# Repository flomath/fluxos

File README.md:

# About
Fluxos is a tiny monolithic operating system for audio applications. Its an educational project at Vorarlberg University of Applied Sciences and features a simple scheduler, virtual memory management and a basic audio application on top.

## Documentation
Find a detailed documentation of this project on the github pages [http://flomath.github.io/fluxos/](http://flomath.github.io/fluxos/).

## Project status

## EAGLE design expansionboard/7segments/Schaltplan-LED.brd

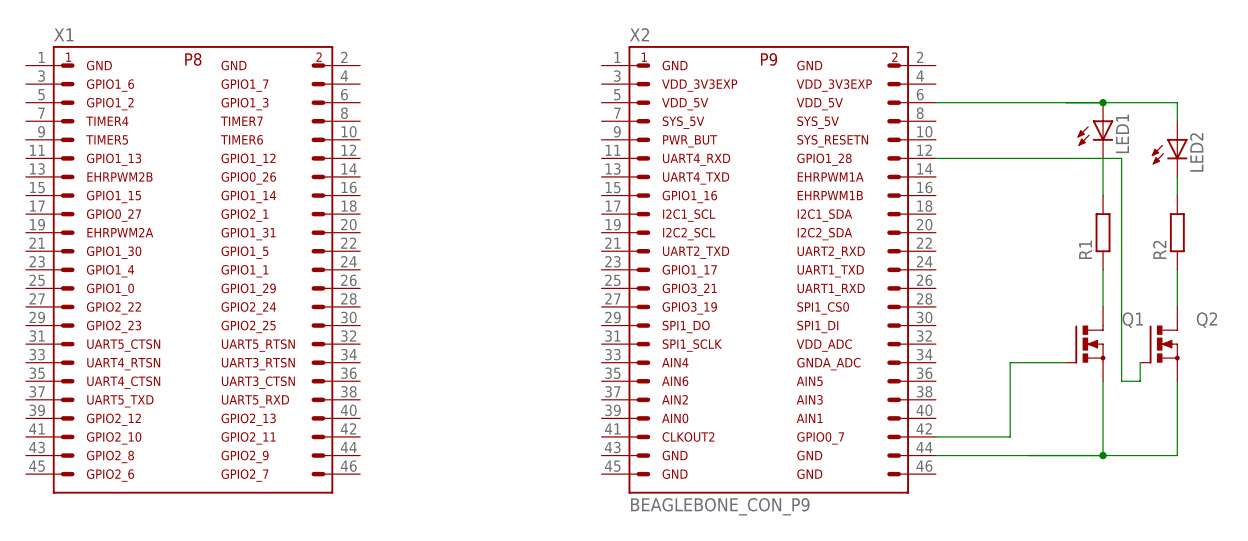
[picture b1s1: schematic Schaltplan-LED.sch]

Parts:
LED1, LED2: LEDCHIP-LED0603; CHIP-LED0603
Q1, Q2: N-MOSFET-SO8S; SO-08
R1, R2: R-EU_R0603; R0603
X1: BEAGLEBONE_CON_P8; 23X2_2-54
X2: BEAGLEBONE_CON_P9; 23X2_2-54

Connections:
unnamed: LED1.A, LED2.A, X2.6
unnamed: LED1.C, R1.2
unnamed: Q1.4 (G), X2.42
unnamed: Q1.5 (D), Q1.6 (D), Q1.7 (D), Q1.8 (D), R1.1
unnamed: Q1.1 (S), Q1.2 (S), Q1.3 (S), Q2.1 (S), Q2.2 (S), Q2.3 (S), X2.44
unnamed: LED2.C, R2.2
unnamed: Q2.4 (G), X2.12
unnamed: Q2.5 (D), Q2.6 (D), Q2.7 (D), Q2.8 (D), R2.1

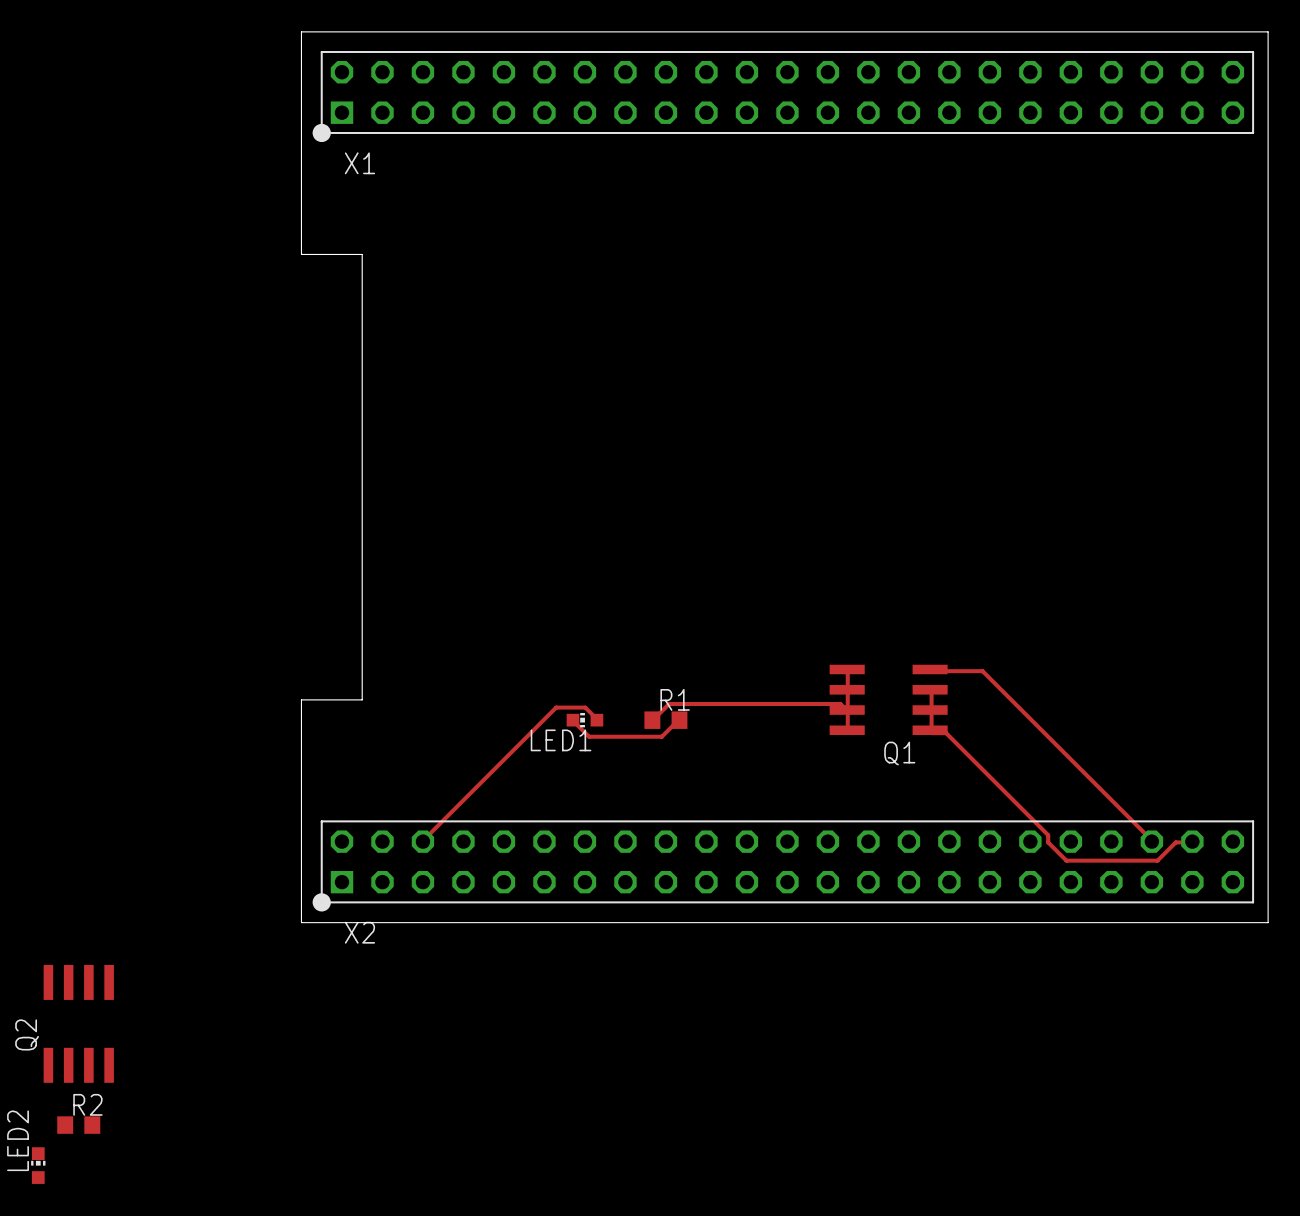
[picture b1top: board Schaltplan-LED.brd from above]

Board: 2 copper layers, 60.6 x 55.9 mm, 9 parts (0 on the bottom side), 8 nets.

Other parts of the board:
U$1: BEAGLEBONE-OUTLINE

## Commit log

2015-02-25 add waffle.io badge
2015-02-25 added github issue badge to readme
2015-02-27 Create gh-pages branch via GitHub
2015-02-27 Trying to add a demo page
2015-02-27 renamed demo
2015-02-27 Added title
2015-02-27 Removed demo.markdown
2015-02-27 removed auto generated files
2015-02-27 Update Readme
    Add link to pages
2015-02-27 Baseurl for fhv-os
2015-02-27 Added gemfile
2015-02-27 removed _site directory
2015-02-27 added new file
2015-02-27 removed pages dir
2015-02-27 added gitignore for _pages and -sites
2015-02-27 wrote the first pages on project management
2015-02-27 updated config and index file
2015-02-27 fixed a bug i previously added to the config file
2015-03-12 setup code composer project
2015-03-12 basic uart based on omap35x programming model
2015-03-13 Added systems page for kernel and omap documentation
2015-03-13 changed the name to fluxos, unified all header styles
2015-03-13 changed name to fluxos (including repository)
2015-03-13 changed name to fluxos
2015-03-13 implemented uart programming model based on omap
2015-03-13 added dma description out of the omap guide
2015-03-18 fixed some compile errors
2015-03-18 Added doxygen file
    Added doxygen for documentation and ignored output file
2015-03-18 added boot.asm and started testing the UART settings
2015-03-18 Added UartDriver
    also commented the hal/uart
2015-03-18 added travis build configuration
2015-03-18 added travis doxygen cmd by github.com/miloyip/rapidjson
2015-03-18 updated travis path
2015-03-18 travis config to skip gcc build
2015-03-18 Added travis status
    Well.. we are not actually building with it, but anyways :wink:
2015-03-18 removed weird badge
2015-03-18 again some updates to the travis configuration
2015-03-18 unfortunately pushed wrong script file
2015-03-18 Fixed Compiler errors
2015-03-18 Update travis
2015-03-18 Cleaned hal
2015-03-18 Updated doxygen build script
2015-03-18 Removed security check
2015-03-18 Automatic doxygen build
2015-03-18 Fixed the beagleboard.cmd in order to hook up our init method, UART init should work by now
2015-03-18 Changed doxygen command
2015-03-18 Revert "Automatic doxygen build"
    This reverts commit d3dead3f54b3b97974bb6c58bd8f0381ef055f79.
2015-03-18 Revert "Automatic doxygen build"
    This reverts commit 58535501b95a1a945c862df11eb9ca8b59eb89c9.
2015-03-19 added RS232 section in documentation
2015-03-19 Update doxygen command for travis
2015-03-19 Fixed forgotten path
2015-03-19 Updating doxygen command again
2015-03-19 restructured hal, added missing uart methods
2015-03-19 Update doxygen command for travis again...
2015-03-19 Fixed paths
2015-03-19 Use newer doxygen version
2015-03-19 Fixed input path
2015-03-19 Add .nojekyll file to Doxygen Folder
2015-03-19 Add .nojekyll file to Doxygen Folder (different function)
2015-03-19 Updating doxygen the last time
2015-03-19 HAL-layer prototype
2015-03-19 Adding nojekyll file to top directory
2015-03-19 Including doxygen
2015-03-19 Including doxygen #2
2015-03-19 Adding .nojekyll again for tests
2015-03-19 deleted nojekyll again
2015-03-19 Adding .nojekyll for testing purposes
2015-03-19 Deleting it...
2015-03-19 Update _config.yml
    test for keeping the files in doxygen directory
2015-03-19 Update _config.yml
    further test for keeping files
2015-03-19 Update _config.yml
    fixed typo
2015-03-19 refactored the directory layout, added common dir for generic implementations
2015-03-19 Update _config.yml
    local running jekyll
2015-03-19 added first version of gp timers
2015-03-20 UART sending
    - Fixed #3
2015-03-25 fixed compiler error
2015-03-25 Update README.md
    fixed url to new repository
2015-03-25 first version of scheduler and process structure
2015-03-25 updated main for ccs project
2015-03-25 reversed everything i did today - didn't think much about it i guess
2015-03-26 groundwork for upcoming context switches with mmu #7
2015-03-26 added timer init and start methods #13
2015-03-26 timer init #13
2015-03-26 Use 32Bitmask for Registers
2015-03-26 First interrupts occuring
    Howver, they are not the ones we want ...
2015-03-26 fixed end of line error
2015-03-26 Implementing enable interrupt method
    Anyway it is not used yet
2015-03-26 info about timer
2015-03-26 moved interface methods to common, added disable interrupt method
2015-03-27 changed about section in readme
2015-03-27 fixed a register define #13
2015-03-27 Fixed Interrupt Stack
2015-03-27 Starting the timer
2015-03-27 Testing timers
2015-03-28 Interrupt Callbacks are now called by the IRQ Handler
2015-03-28 Adding header file for Power Management
    However not used, because everything is ENABLED by default
2015-04-02 new timer setting as in reference guide p.2615
2015-04-02 Ensure correct register size
2015-04-02 added timer implementation details
2015-04-02 updated scrum sprints
2015-04-02 Receiving (only) first character
    - by a timeout
    - exception because reentering the ISR
2015-04-08 Removed #pragma TASK because it won't save the LR from the IRQ so that it won't go back
2015-04-08 added timers 3 to 9, but only working as 1ms ticks
2015-04-09 Updated documentation: Interrupts
    Added interrupts to the documentation
2015-04-09 Fixed path for GH Pages
2015-04-09 did nothing
2015-04-09 scheduler running with timer interval, except if you add an endless loop in your tasks (do we need to leave the interrupt mode first?)
2015-04-09 First prototype of mmu, mmu can be enabled now - settings have to be defined correctly
2015-04-09 Added UART as Process
2015-05-13 added expansion board brd files for eagle
2015-05-13 WIP Temporarly save Context
2015-05-13 added clock and gpio using programming model, not yet tested
2015-05-14 prototype of mmu and memory manager (need to be tested + dabt handler not implemented yet)
2015-05-14 gpio and button is triggering a interrupt, leds do not work currently
2015-05-14 WIP Context Switch
2015-05-14 "mmu enable" is working now, introduced NULL and bool type
2015-05-14 removed unnecessary functions
2015-05-14 added source files for mcbsp
2015-05-20 l2 and page frames
2015-05-20 WIP Context Load seems to work
2015-05-20 L1, L2 and page frames (waiting for correct interrupt), added process functions to mmu
2015-05-22 Scheduling between the first 3 Processes works, however the value in the USER-LR of PID#0 is 0, therefore a DataAbort Exception occurs
2015-05-23 moved regions, added some todos
2015-05-23 added system calls (working,except after switching back to context)
2015-05-23 Context is now saved to Stack and load from there,
    however I still get some PABT Exceptions after one round
2015-05-23 Disabled printfs ... Seems to be working now
2015-05-24 CS working :)
2015-05-28 adjusted for new process struc
2015-05-29 init commit for filesystem
2015-05-30 save of current state, dabts working -> l2 gets overwritten!
2015-05-30 mmu is working now (seems to) - killing processes still not implemented
2015-05-30 clear the interrupt flag afterwards, otherwise interrupt is called twice
2015-06-03 mmu can kill a process now
2015-06-04 no function call for setting a bit
2015-06-04 Audio development started: Enabled MCBSP2
2015-06-04 removed unused function, printfs..
2015-06-04 extended hal to 32bit, added mmcsd settings
2015-06-04 mmcsd programming guide no. 2
2015-06-07 send commands, and following the programming guide - part 3
2015-06-10 i2c header added
    We will need TPS65950 for audio which is controlled by I2C
2015-06-10 moved irq clearing, process exit handler(need to be extracted as syscall)
2015-06-10 Revert "Merge branch 'filesystem' of https://github.com/flomath/fluxos"
    This reverts commit 4ed08148a070b577ef70f09ed236475965b2041b, reversing
    changes made to 992f4ce8624f184f5e2a38e5c143661ae7149a18.
2015-06-10 fixed reading value calls
2015-06-10 Inline must be in header
2015-06-10 Project settings
2015-07-01 Started a first process... I guess
2015-07-01 missing file
2015-07-01 setting up mmcsd, next step: send cmd
2015-07-02 Tested UART
2015-07-02 working on audio initialization
2015-07-02 process killing is working now
2015-07-02 Still working on audio configuration
2015-07-02 still working on detecting sd card, failing at busy flag
2015-07-02 wrong clock selected, still no luck
2015-07-03 console/uart test
2015-07-03 forgot to commit new files
2015-07-03 work in progress
2015-07-03 working on mmcsd settings
2015-07-03 New Application added
2015-07-03 changed sysapi
2015-07-03 Changed Project settings to enable hex output
2015-07-03 Application One added and Build problem fixed
2015-07-03 Changed Stack Position
2015-07-03 Print from Application
2015-07-03 Added syscall for loading processes, changed loader function
2015-07-03 working version beta 0.1
2015-07-03 removed unused pcb params
2015-07-03 again, some changes - no luck
2015-07-03 working copy of detecting card
2015-07-03 read and write methods for sd card
2015-07-03 Created a semaphore
2015-07-03 Creating and Destroying Semaphores
2015-07-04 uart_read in console has to checked
2015-07-04 Using semaphore for UART; Problem: irqs do not occur during syscall
2015-07-04 some changes, no luck again
2015-07-04 semaphore seems to be working when printfs are there. Without them it won't work
2015-07-04 removed while from syscall
2015-07-04 Fixing hammels mistake
2015-07-04 Working console with echo and greetings
2015-07-04 improved mmc(not working yet)
2015-07-05 i2c, failed at writing 16 bit in hal - audio and led now works
2015-07-05 fixed HAL bitmask write failure
2015-07-05 Refactored I²C
2015-07-05 adjusted whole mmcsd process (untested)
2015-07-05 Audio Refactored and All My Ducks added
2015-07-05 refactored tps for audio and LEd
2015-07-05 sd card read is working now
2015-07-05 Release 1.0
2015-07-05 Started presentation
2015-07-05 added memory map
2015-07-05 adjustments
2015-07-05 fixed bug in scheduler (max 8 tasks running)
2015-07-05 updated memory map
2015-07-05 added documentation
2015-07-05 Using semaphore for console
2015-07-05 added filesystem, console can execute bin (only once)
2015-07-06 integrating asm folders in ccs
2015-07-06 added some todos
2015-07-06 MMU docu (not finished yet)
2015-07-07 changed mapping of process
2015-07-07 moved images, changed memory map
2015-07-12 Scheduler, IPC and Todo's added
2015-07-12 Typos
2015-07-13 mmu image reference
2015-07-17 updated documentation
2015-07-18 Documentation, typos fixed, improved content
2015-07-18 further mmu docu improvements
2015-07-18 added filesystem docu (with mmc)
2015-07-18 extracted uart from system - interrupts/timer has to be extracted as well
2015-07-18 fixed some links
2015-07-19 interrupt -> todo: syscall
2015-07-19 syscalls
2015-07-19 todo for mmu
2015-07-19 reverted max processes back to 8..
2015-07-22 restructuring, added audio
2015-07-23 added audio application information
2015-07-24 renamed system to timer
2015-07-25 finished audio chapter
2015-07-26 added loader section, added code section to filesystem, some modifications at interrupts
2015-07-27 added example video
2015-07-27 Update 2015-07-18-Audio-Application.md
    added greetings documentation
2015-07-27 sort pages
2015-07-27 fixed file naming
2015-07-27 docu all together
2015-07-27 docu for pandoc + pdf
2015-07-29 fixed spelling errors
2015-07-29 added first release presentation

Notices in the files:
parts and their libraries:
BeagleBone: connector 23x2 2.54  CC0
BeagleBone: License:  CC-Zero
